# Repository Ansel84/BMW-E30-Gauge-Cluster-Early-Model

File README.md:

# BMW E30 Gauge Cluster Early Model
The goal for this project is to reverse engineer every PCB in the gauge cluster for early model year BMW E30's. This includes the main PCB referred to as the "Nexus" board and the smaller boards that are part of the tachometer and speedometer gauge assemblies. The SI (Service Interval) board has already been successfully reverse engineered and improved by Fabian Gmeiner. His project is linked below. 

## Fabian Gmeiner's SI board project:
https://github.com/FabianGmeiner/BMW_E30_SI_Board

# Progress
08/17/25
The Nexus board is the only board that has been started so far, the other project files are placeholders for now. The Nexus board is nearly complete but still needs to be touched up slightly before being sent off to a manufacturer. Things like via placements, and bulb footprints need to be adjusted as well as verifying the board cut hole locations via a laser cut version. -Ansel84

08/20/25
Begun laser cutting Nexus board tests to ensure that the layout will work before sending off gerbers to be made. Will work on other boards in the meantime. -Ansel84

08/25/25
Started on the speedometer board. Decoded the schematic and layout for the simple speedometer circuit (no O2 sensor indicator circuit). -Ansel84

08/26 - 29/25
Had to find other examples as the one I have only is part of the full circuit. Was able to figure out the circuit from pictures provided by a discord member. -Ansel84

08/30/25
Hall effect sensor PCB replicated. NOTE: if this is ever produced it is only compatible with the Speedometer PCB designed in this project, not compatible with the original board. -Ansel84

09/01/25
speedometer PCB schematic completed. -Ansel84

09/03/25
EG schematic completed. -Ansel84

10/20/25
First run of Nexus board PCB's arrived from JLCPCB. Unfortunately the Connector IV and connector V footprints are not compatible with the original connectors. Also, the fuel gauge location is not quite right, as well as a few lights and screw hole locations. Finally, J1 (Blue connector) location was slightly off. A second set of PCB's will be ordered hopefully fixing these issues. -Ansel84

10/30/25
Updated footprint library to include the coding plug switch and connectors to the EG board. Component locations are in place on this board now. NOTE: double check the locations of J1 and J2 to ensure they are exact, they are only approximate now. -Ansel84

11/01/25
Component locations are complete on the tachometer pcb layout. 

# Late Model Clusters:
If you have a late model cluster and need parts for that, check out the progress of the late model project here: https://github.com/Ansel84/BMW-E30-Gauge-Cluster-Late-Model

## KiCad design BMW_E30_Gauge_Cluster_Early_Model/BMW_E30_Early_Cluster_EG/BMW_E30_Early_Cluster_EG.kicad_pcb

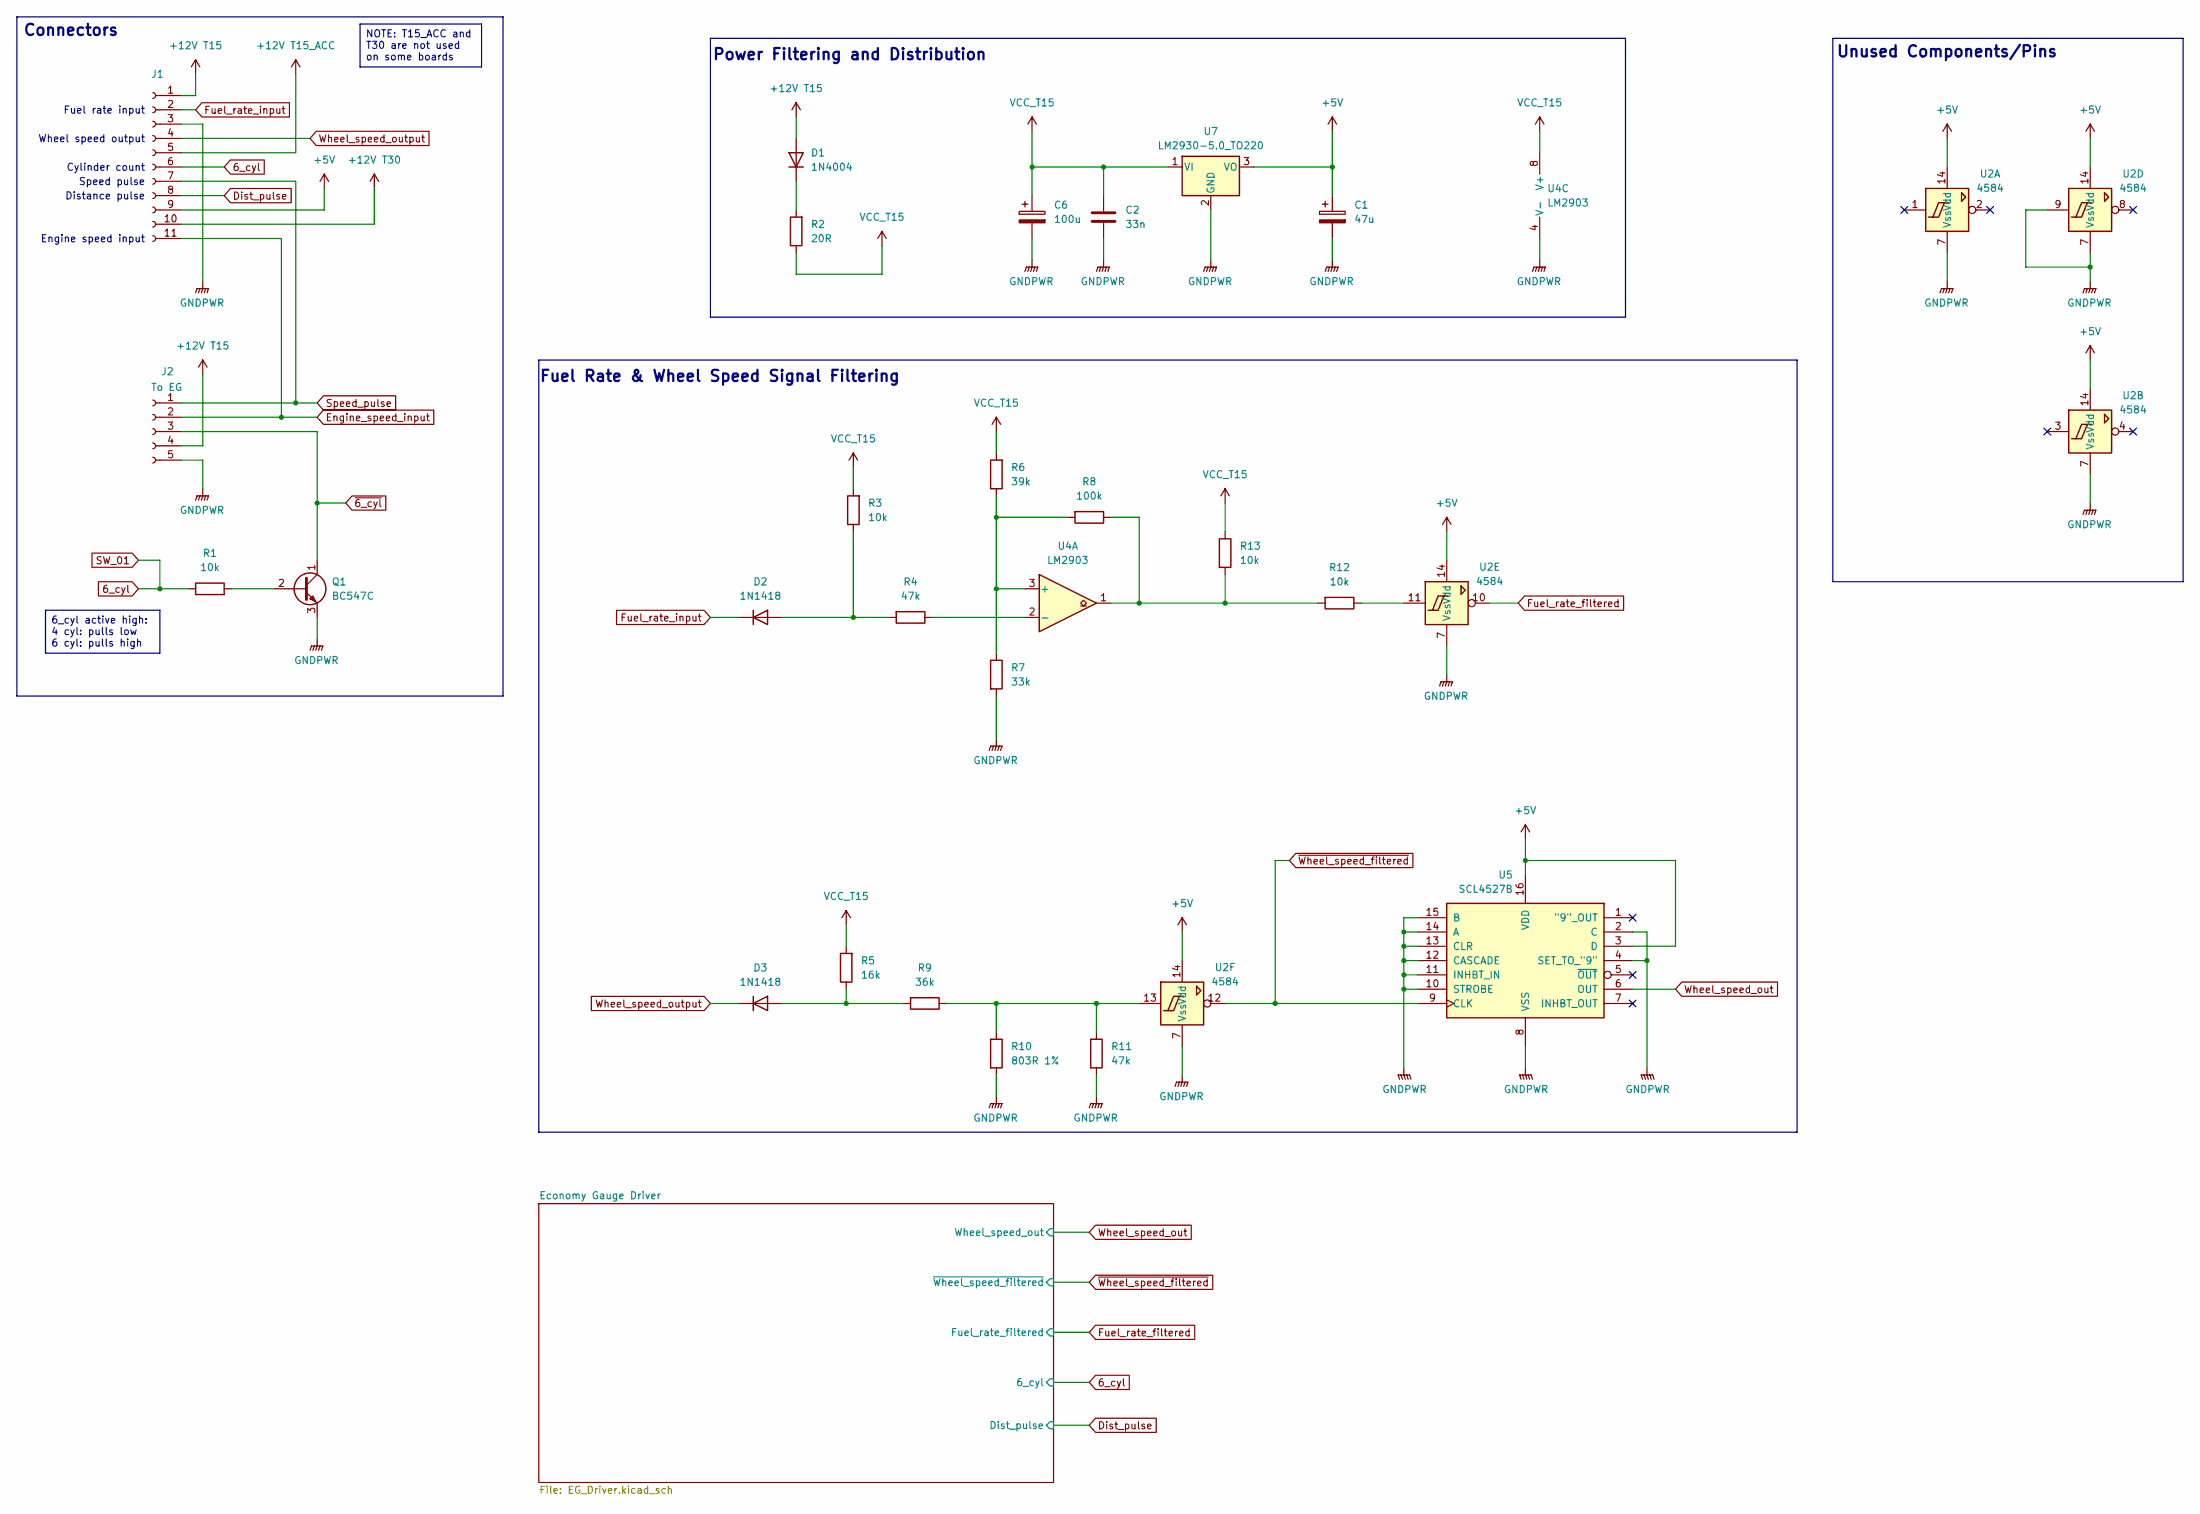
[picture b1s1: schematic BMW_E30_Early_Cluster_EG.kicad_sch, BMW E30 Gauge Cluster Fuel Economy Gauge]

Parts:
C1: 47u; CP_Radial_Tantal_D5.0mm_P2.50mm; Voltage 6.3
C2: 33n; C_Rect_L13.0mm_W4.0mm_P10.00mm_FKS3_FKP3_MKS4; Voltage 250
C6: 100u; CP_Radial_D8.0mm_P5.00mm; Voltage 16
D1: 1N4004; D_DO-41_SOD81_P10.16mm_Horizontal
D2, D3: 1N1418; D_DO-34_SOD68_P10.16mm_Horizontal
J1: Conn_01x11_Socket; ConnectorIV_EG_Socket
J2: To EG; EG_Tach_Socket
Q1: BC547C; TO-92L_Wide
R1, R3, R12, R13: 10k; R_Axial_DIN0207_L6.3mm_D2.5mm_P10.16mm_Horizontal
R2: 20R; R_Axial_DIN0309_L9.0mm_D3.2mm_P20.32mm_Horizontal
R4, R11: 47k; R_Axial_DIN0207_L6.3mm_D2.5mm_P10.16mm_Horizontal
R5: 16k; R_Axial_DIN0207_L6.3mm_D2.5mm_P10.16mm_Horizontal
R6: 39k; R_Axial_DIN0207_L6.3mm_D2.5mm_P10.16mm_Horizontal
R7: 33k; R_Axial_DIN0207_L6.3mm_D2.5mm_P10.16mm_Horizontal
R8: 100k; R_Axial_DIN0207_L6.3mm_D2.5mm_P10.16mm_Horizontal
R9: 36k; R_Axial_DIN0207_L6.3mm_D2.5mm_P10.16mm_Horizontal
R10: 803R 1%; R_Axial_DIN0207_L6.3mm_D2.5mm_P10.16mm_Horizontal
U2: 4584; DIP-14_W7.62mm_Socket_LongPads
U4: LM2903; DIP-8_W7.62mm_Socket
U5: SCL4527B; DIP-16_W7.62mm_Socket_LongPads
U7: LM2930-5.0_TO220; TO-220-3_Vertical

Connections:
6_cyl: J1.6, R1.1; also elsewhere on the board
+5V: C1.1, J1.9, U2.14 (Vdd), U5.3 (D), U5.16 (VDD), U7.3 (VO); also elsewhere on the board
+12V T15: D1.2 (A), J1.1, J2.4
+12V T15_ACC: J1.5
+12V T30: J1.10
Dist_pulse: J1.8; also elsewhere on the board
Engine_speed_input: J1.11, J2.2
Fuel_rate_filtered: U2.10; also elsewhere on the board
Fuel_rate_input: D2.1 (K), J1.2
GNDPWR: C1.2, C2.2, C6.2, J1.3, J2.5, Q1.3 (E), R7.2, R10.2, R11.2, U2.7 (Vss), U2.9, U4.4 (V-), U5.2 (C), U5.4 (SET_TO_"9"), U5.8 (VSS), U5.10 (STROBE), U5.11 (INHBT_IN), U5.12 (CASCADE), U5.13 (CLR), U5.14 (A), U5.15 (B), U7.2 (GND); also elsewhere on the board
unnamed: D1.1 (K), R2.2
unnamed: D2.2 (A), R3.1, R4.2
unnamed: D3.2 (A), R5.1, R9.2
unnamed: Q1.2 (B), R1.2
unnamed: R9.1, R10.1, R11.1, U2.13
unnamed: R12.1, U2.11
unnamed: R8.1, R12.2, R13.2, U4.1
unnamed: R6.1, R7.1, R8.2, U4.3 (+)
unnamed: R4.1, U4.2 (-)
Speed_pulse: J1.7, J2.1
VCC_T15: C2.1, C6.1, R2.1, R3.2, R5.2, R6.2, R13.1, U4.8 (V+), U7.1 (VI); also elsewhere on the board
Wheel_speed_out: U5.6 (OUT); also elsewhere on the board
Wheel_speed_output: D3.1 (K), J1.4
~6_cyl: J2.3, Q1.1 (C)
~Wheel_speed_filtered: U2.12, U5.9 (CLK); also elsewhere on the board

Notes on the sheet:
Speed pulse
Power Filtering and Distribution
Distance pulse
Fuel rate input
Wheel speed output
Fuel Rate & Wheel Speed Signal Filtering
Unused Components/Pins
Connectors
Engine speed input
Cylinder count
6_cyl active high: 4 cyl: pulls low 6 cyl: pulls high
NOTE: T15_ACC and T30 are not used on some boards

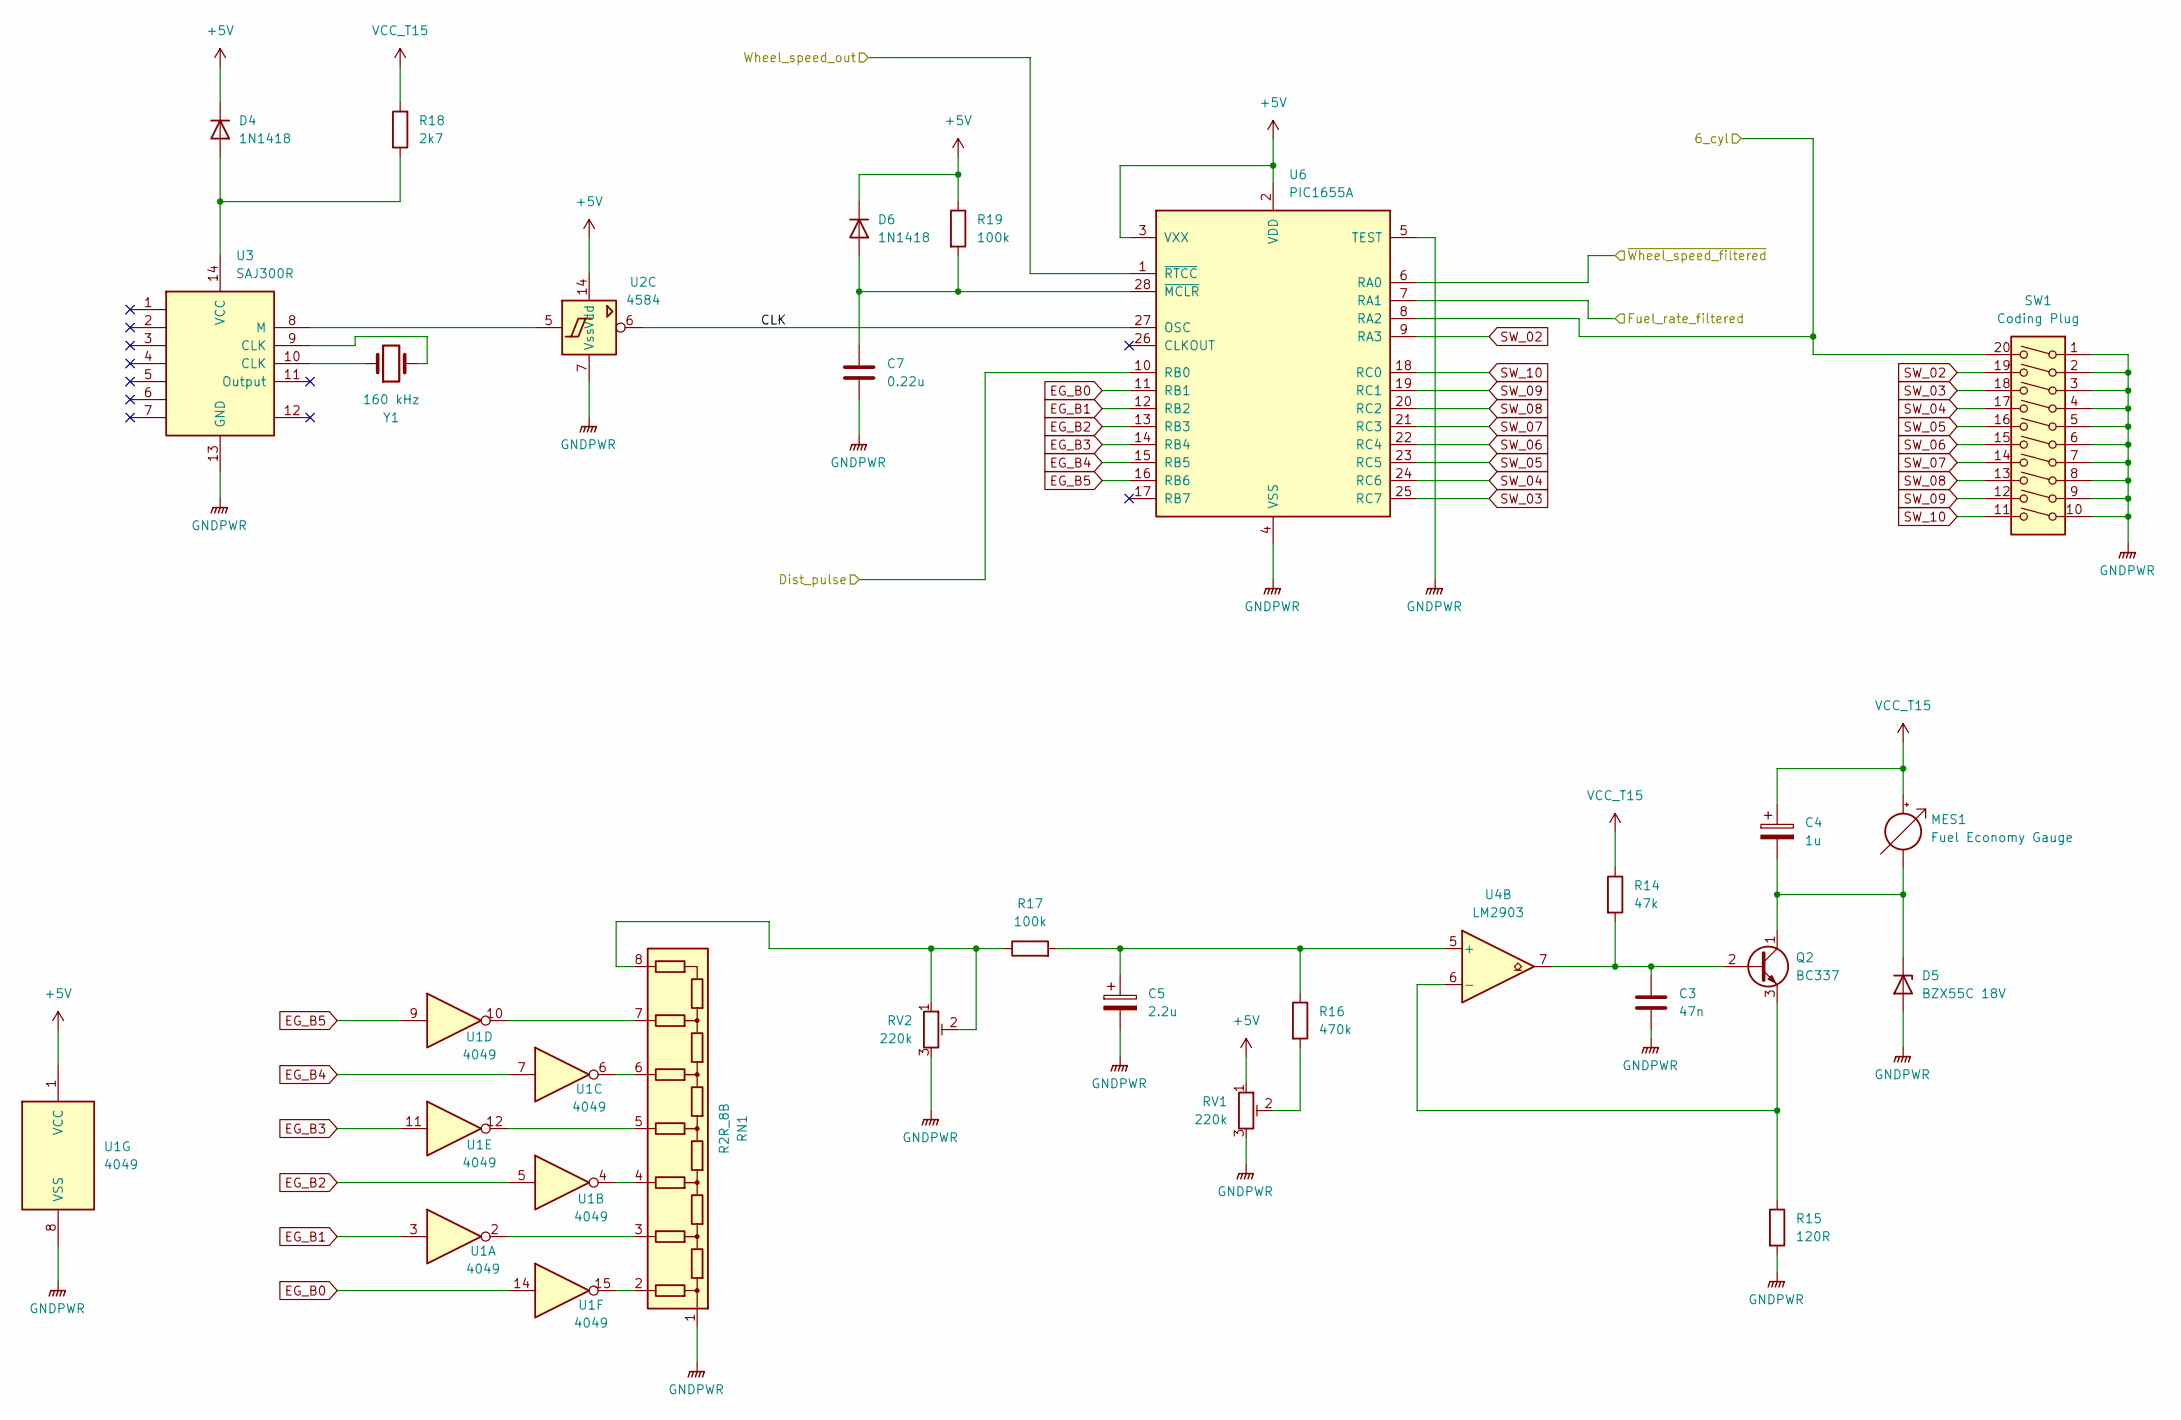
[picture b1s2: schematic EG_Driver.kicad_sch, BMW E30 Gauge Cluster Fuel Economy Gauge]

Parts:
C3: 47n; C_Rect_L13.0mm_W4.0mm_P10.00mm_FKS3_FKP3_MKS4; Voltage 250
C4: 1u; CP_Radial_Tantal_D5.0mm_P2.50mm; Voltage 35
C5: 2.2u; CP_Radial_Tantal_D4.5mm_P2.50mm; Voltage 25
C7: 0.22u; C_Rect_L10.0mm_W3.0mm_P7.50mm_FKS3_FKP3; Voltage 63
D4, D6: 1N1418; D_DO-34_SOD68_P10.16mm_Horizontal
D5: BZX55C 18V; D_DO-34_SOD68_P10.16mm_Horizontal
MES1: Fuel Economy Gauge; Connector_EG
Q2: BC337; TO-92L_Wide
R14: 47k; R_Axial_DIN0207_L6.3mm_D2.5mm_P10.16mm_Horizontal
R15: 120R; R_Axial_DIN0207_L6.3mm_D2.5mm_P10.16mm_Horizontal
R16: 470k; R_Axial_DIN0207_L6.3mm_D2.5mm_P10.16mm_Horizontal
R17, R19: 100k; R_Axial_DIN0207_L6.3mm_D2.5mm_P10.16mm_Horizontal
R18: 2k7; R_Axial_DIN0207_L6.3mm_D2.5mm_P10.16mm_Horizontal
RN1: R2R_8B; R_Array_SIP8
RV1, RV2: 220k; Potentiometer_ACP_CA9-H2,5_Horizontal
SW1: Coding Plug; Coding_Plug
U1: 4049; DIP-16_W7.62mm_Socket
U2: 4584
U3: SAJ300R; DIP-14_W7.62mm_Socket_LongPads
U4: LM2903; DIP-8_W7.62mm_Socket
U6: PIC1655A; DIP-28_W15.24mm
Y1: 160 kHz; Crystal_HC49-U_Vertical

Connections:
6_cyl: SW1.20, U6.8 (RA2); also elsewhere on the board
+5V: D4.1 (K), D6.1 (K), R19.1, RV1.1, U1.1 (VCC), U2.14 (Vdd), U6.2 (VDD), U6.3 (VXX); also elsewhere on the board
/Economy Gauge Driver/CLK: U2.6, U6.27 (OSC)
Dist_pulse: U6.10 (RB0); also elsewhere on the board
EG_B0: U1.14, U6.11 (RB1)
EG_B1: U1.3, U6.12 (RB2)
EG_B2: U1.5, U6.13 (RB3)
EG_B3: U1.11, U6.14 (RB4)
EG_B4: U1.7, U6.15 (RB5)
EG_B5: U1.9, U6.16 (RB6)
Fuel_rate_filtered: U6.7 (RA1); also elsewhere on the board
GNDPWR: C3.2, C5.2, C7.2, D5.2 (A), R15.2, RN1.1 (Bit_out), RV1.3, RV2.3, SW1.1, SW1.2, SW1.3, SW1.4, SW1.5, SW1.6, SW1.7, SW1.8, SW1.9, SW1.10, U1.8 (VSS), U2.7 (Vss), U3.13 (GND), U6.4 (VSS), U6.5 (TEST); also elsewhere on the board
unnamed: D4.2 (A), R18.1, U3.14 (VCC)
unnamed: C4.2, D5.1 (K), MES1.1 (-), Q2.1 (C)
unnamed: C7.1, D6.2 (A), R19.2, U6.28 (~MCLR)
unnamed: C3.1, Q2.2 (B), R14.2, U4.7
unnamed: Q2.3 (E), R15.1, U4.6 (-)
unnamed: R16.2, RV1.2
unnamed: RN1.2 (R1), U1.15
unnamed: RN1.3 (R2), U1.2
unnamed: RN1.4 (R3), U1.4
unnamed: RN1.5 (R4), U1.12
unnamed: RN1.6 (R5), U1.6
unnamed: RN1.7 (R6), U1.10
unnamed: R17.1, RN1.8 (R7), RV2.1, RV2.2
unnamed: U3.9 (CLK), Y1.2
unnamed: U3.10 (CLK), Y1.1
unnamed: U2.5, U3.8 (M)
unnamed: C5.1, R16.1, R17.2, U4.5 (+)
SW_02: SW1.19, U6.9 (RA3)
SW_03: SW1.18, U6.25 (RC7)
SW_04: SW1.17, U6.24 (RC6)
SW_05: SW1.16, U6.23 (RC5)
SW_06: SW1.15, U6.22 (RC4)
SW_07: SW1.14, U6.21 (RC3)
SW_08: SW1.13, U6.20 (RC2)
SW_09: SW1.12, U6.19 (RC1)
SW_10: SW1.11, U6.18 (RC0)
VCC_T15: C4.1, MES1.2 (+), R14.1, R18.2; also elsewhere on the board
Wheel_speed_out: U6.1 (~RTCC); also elsewhere on the board
~Wheel_speed_filtered: U6.6 (RA0); also elsewhere on the board

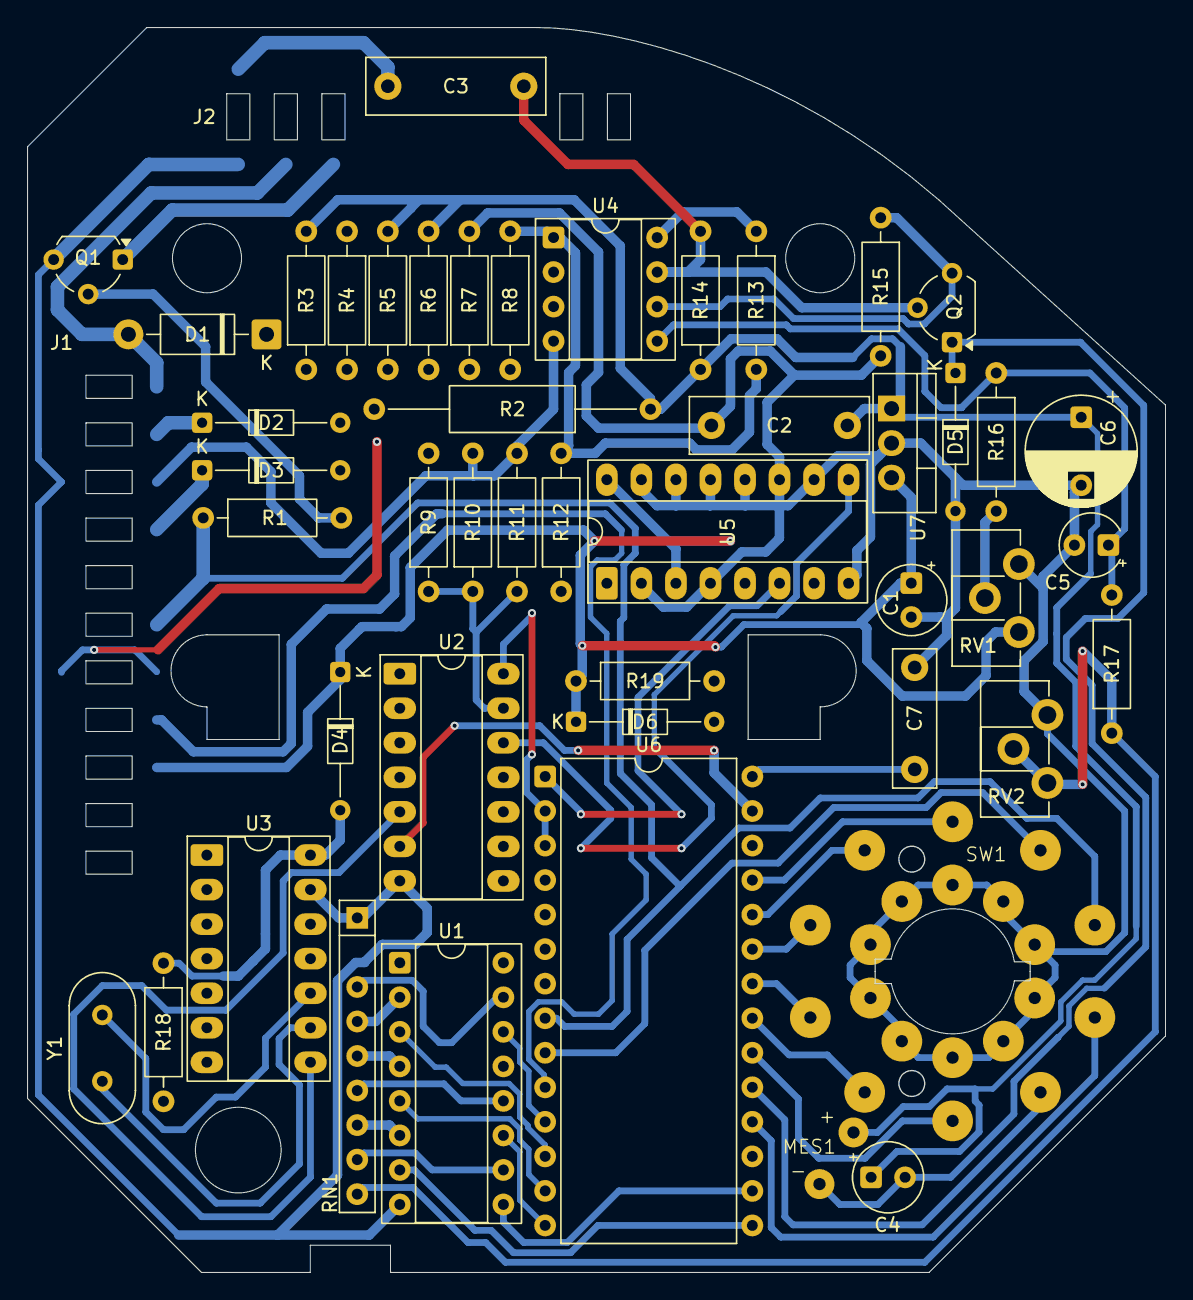
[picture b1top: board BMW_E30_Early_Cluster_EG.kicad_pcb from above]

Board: 2 copper layers, 83.7 x 91.6 mm, 49 parts (0 on the bottom side), 56 nets.

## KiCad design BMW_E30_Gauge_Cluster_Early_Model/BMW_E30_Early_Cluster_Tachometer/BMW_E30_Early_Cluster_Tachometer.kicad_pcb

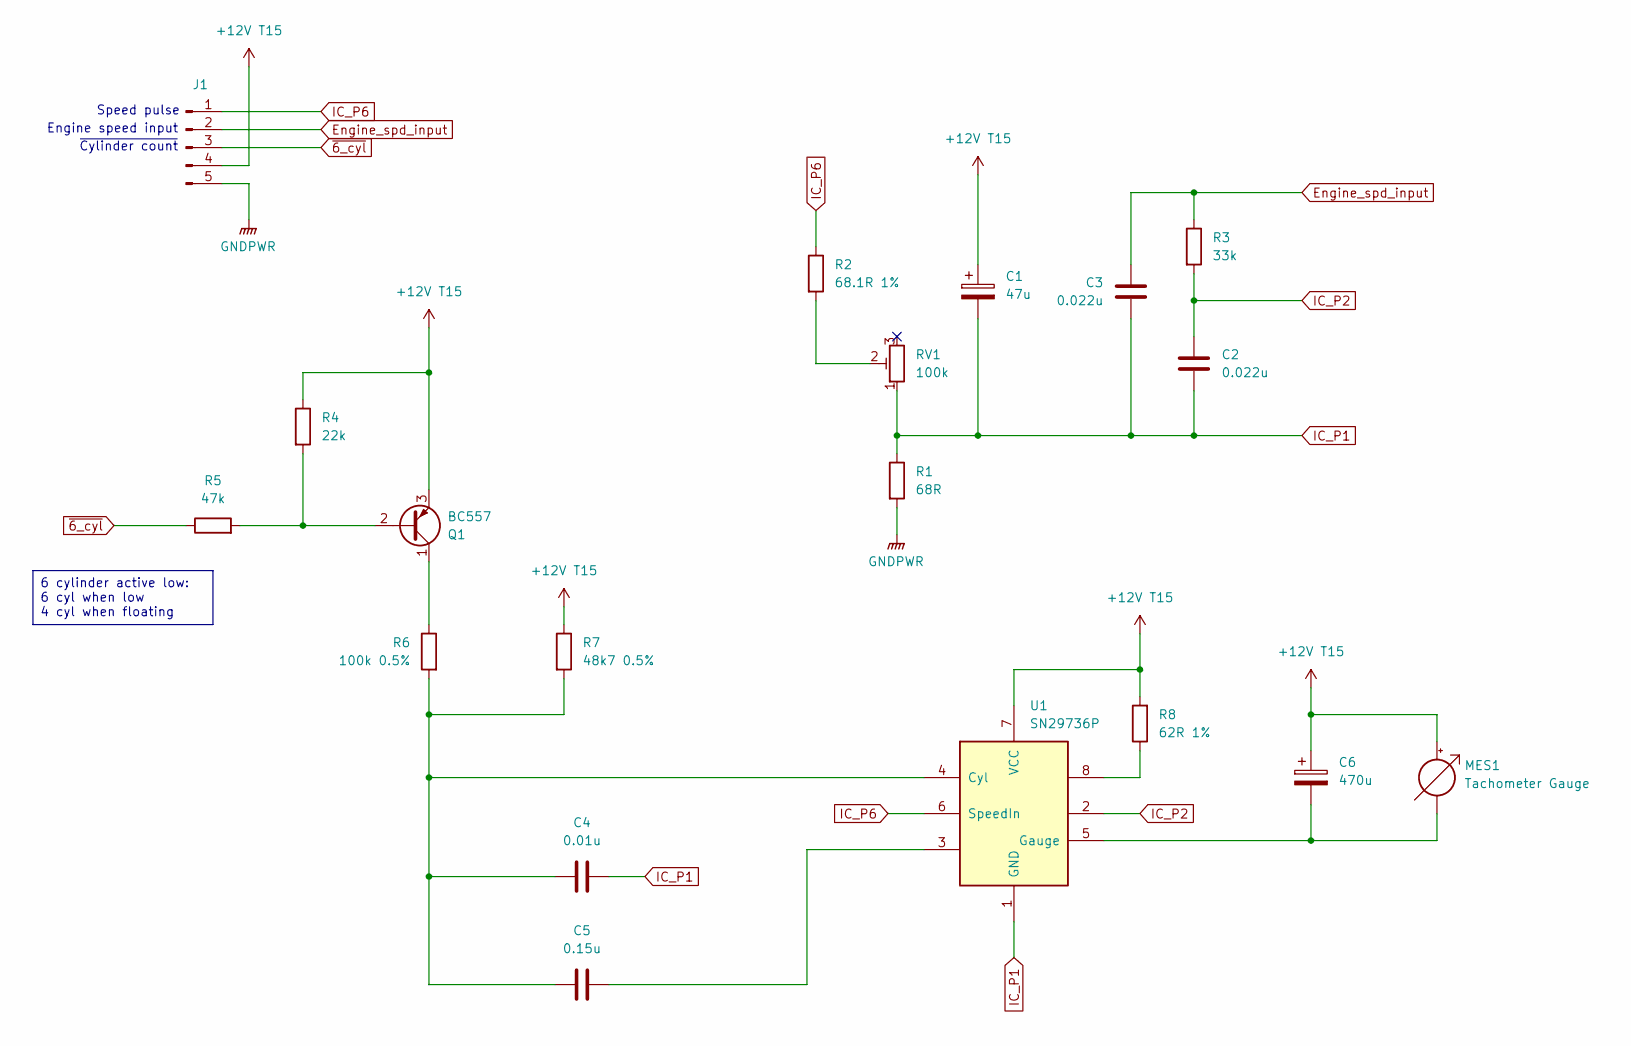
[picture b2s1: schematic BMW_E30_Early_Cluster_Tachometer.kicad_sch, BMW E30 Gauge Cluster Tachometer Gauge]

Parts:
C1: 47u; CP_Axial_L11.0mm_D6.0mm_P18.00mm_Horizontal
C2, C3: 0.022u; C_Axial_L12.0mm_D6.5mm_P15.00mm_Horizontal
C4: 0.01u; C_Disc_D5.0mm_W2.5mm_P5.00mm
C5: 0.15u; C_Axial_L12.0mm_D6.5mm_P15.00mm_Horizontal
C6: 470u; CP_Axial_L25.0mm_D10.0mm_P30.00mm_Horizontal
J1: Conn_01x05_Pin; EG_Tach_Pins
MES1: Tachometer Gauge; Connector_Tach
Q1: BC557; TO-92_Wide
R1: 68R; R_Axial_DIN0411_L9.9mm_D3.6mm_P15.24mm_Horizontal
R2: 68.1R 1%; R_Axial_DIN0207_L6.3mm_D2.5mm_P7.62mm_Horizontal
R3: 33k; R_Axial_DIN0207_L6.3mm_D2.5mm_P7.62mm_Horizontal
R4: 22k; R_Axial_DIN0207_L6.3mm_D2.5mm_P7.62mm_Horizontal
R5: 47k; R_Axial_DIN0207_L6.3mm_D2.5mm_P7.62mm_Horizontal
R6: 100k 0.5%; R_Axial_DIN0207_L6.3mm_D2.5mm_P7.62mm_Horizontal
R7: 48k7 0.5%; R_Axial_DIN0207_L6.3mm_D2.5mm_P7.62mm_Horizontal
R8: 62R 1%; R_Axial_DIN0309_L9.0mm_D3.2mm_P15.24mm_Horizontal
RV1: 100k; Potentiometer_Piher_PT-10-V10_Vertical
U1: SN29736P; DIP-8_W7.62mm_Socket_LongPads

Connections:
+12V T15: C1.1, C6.1, J1.4, MES1.2 (+), Q1.3 (E), R4.1, R7.1, R8.2, U1.7 (VCC)
Engine_spd_input: C3.1, J1.2, R3.1
GNDPWR: J1.5, R1.2
IC_P1: C1.2, C2.2, C3.2, C4.1, R1.1, RV1.1, U1.1 (GND)
IC_P2: C2.1, R3.2, U1.2
IC_P6: J1.1, R2.1, U1.6 (SpeedIn)
unnamed: C5.1, U1.3
unnamed: C6.2, MES1.1 (-), U1.5 (Gauge)
unnamed: Q1.2 (B), R4.2, R5.2
unnamed: Q1.1 (C), R6.1
unnamed: R2.2, RV1.2
unnamed: R8.1, U1.8
unnamed: C4.2, C5.2, R6.2, R7.2, U1.4 (Cyl)
~6_cyl: J1.3, R5.1

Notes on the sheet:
Speed pulse
Engine speed input
~{Cylinder count}
6 cylinder active low: 6 cyl when low 4 cyl when floating

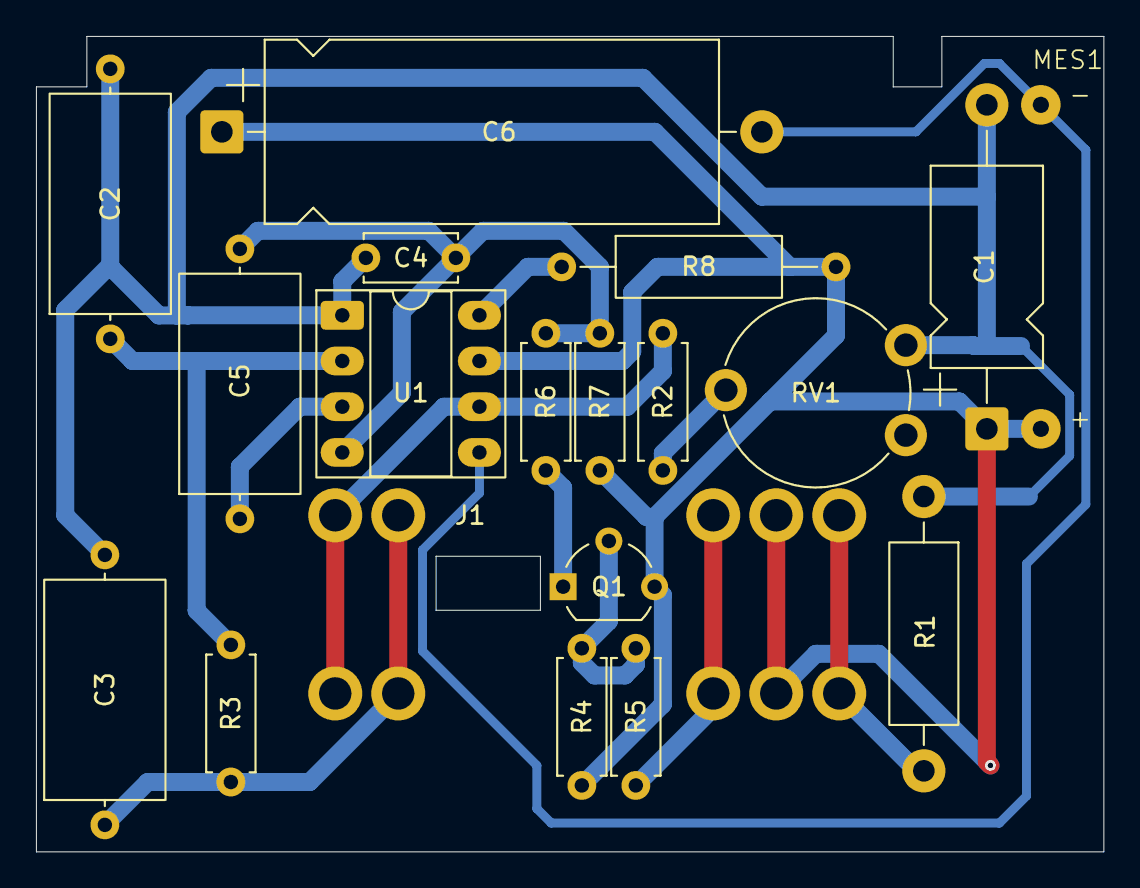
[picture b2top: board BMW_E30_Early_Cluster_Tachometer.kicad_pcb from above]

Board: 2 copper layers, 59.3 x 45.3 mm, 19 parts (0 on the bottom side), 14 nets.

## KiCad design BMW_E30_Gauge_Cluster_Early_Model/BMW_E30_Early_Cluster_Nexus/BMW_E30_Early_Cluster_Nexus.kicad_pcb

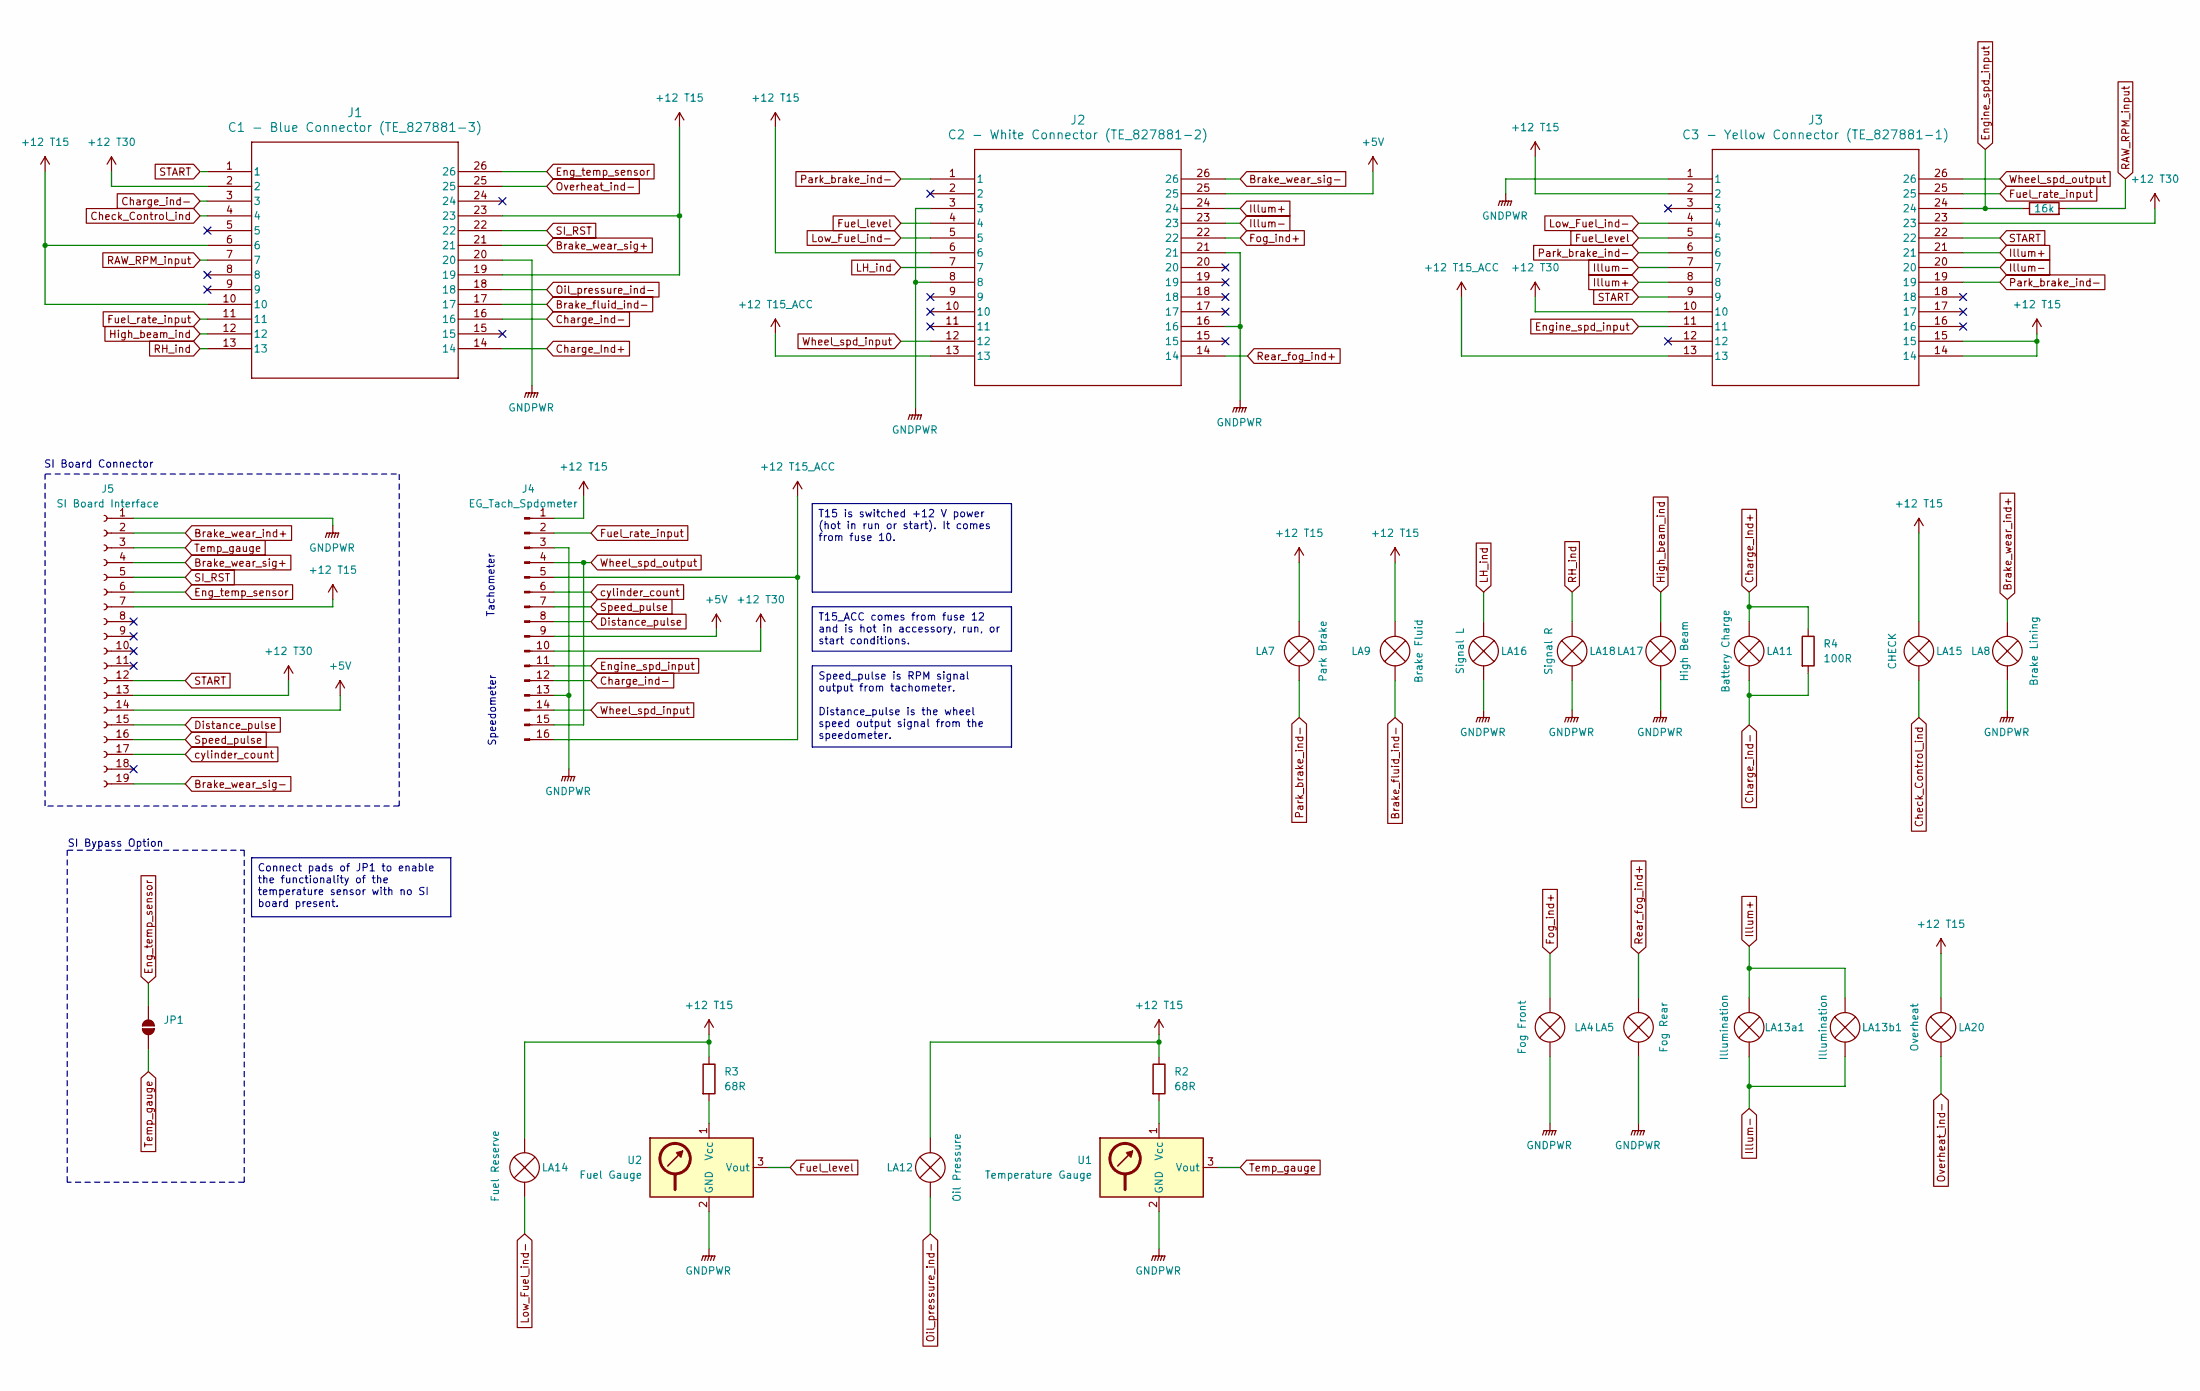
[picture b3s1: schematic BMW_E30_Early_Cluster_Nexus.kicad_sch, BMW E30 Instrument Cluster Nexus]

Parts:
J1: C1 - Blue Connector (TE_827881-3); TE_827881-3; Digikey Part No. 827881-3-ND
J2: C2 - White Connector (TE_827881-2); TE_827881-2; Digikey Part No. A129100-ND
J3: C3 - Yellow Connector (TE_827881-1); TE_827881-1; Digikey Part No. A129099-ND
J4: EG_Tach_Spdometer; ConnectorIV_Early
J5: SI Board Interface; ConnectorV_Early_V2
JP1: SI BYPASS; SolderJumper-2_P1.3mm_Open_RoundedPad1.0x1.5mm
LA4: Fog Front; 2721MF
LA5: Fog Rear; 2721MF
LA7: Park Brake; 2721MF
LA8: Brake Lining; 2721MF
LA9: Brake Fluid; 2721MF
LA11: Battery Charge; 2821MF
LA12: Oil Pressure; 2721MF
LA13a1, LA13b1: Illumination; 2821MF
LA14: Fuel Reserve; 2721MF
LA15: CHECK; 2721MF
LA16: Signal L; 2721MF
LA17: High Beam; 2721MF
LA18: Signal R; 2721MF
LA20: Overheat; 2721MF
R1: 16k; R_Axial_DIN0207_L6.3mm_D2.5mm_P10.16mm_Horizontal; Digikey Part No. CF14JT16K0CT-ND
R2, R3: 68R; R_Axial_DIN0516_L15.5mm_D5.0mm_P20.32mm_Horizontal; Digikey Part No. 2019-PCF1C680K-ND
R4: 100R; R_Axial_DIN0414_L11.9mm_D4.5mm_P15.24mm_Horizontal; Digikey Part No. 541-CMF65100R00FKEBCT-ND
U1: Temperature Gauge; Gauge_Temp
U2: Fuel Gauge; Gauge_Fuel

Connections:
+5V: J2.25, J4.9, J5.14
+12 T15: J1.6, J1.10, J1.19, J1.23, J2.6, J3.2, J3.14, J3.15, J4.1, J5.7, LA7.2 (+), LA9.2 (+), LA12.2 (+), LA14.1 (-), LA15.1 (-), LA20.1 (-), R2.1, R3.1
+12 T15_ACC: J2.13, J3.13, J4.5, J4.16
+12 T30: J1.2, J3.10, J3.23, J4.10, J5.13
Brake_fluid_ind-: J1.17, LA9.1 (-)
Brake_wear_ind+: J5.2, LA8.2 (+)
Brake_wear_sig+: J1.21, J5.4
Brake_wear_sig-: J2.26, J5.19
Charge_Ind+: J1.14, LA11.1 (-), R4.1
Charge_ind-: J1.3, J1.16, J4.12, LA11.2 (+), R4.2
Check_Control_ind: J1.4, LA15.2 (+)
Distance_pulse: J4.8, J5.15
Eng_temp_sensor: J1.26, J5.6, JP1.2 (B)
Engine_spd_input: J3.11, J3.24, J4.11, R1.1
Fog_ind+: J2.22, LA4.1 (-)
Fuel_level: J2.4, J3.5, U2.3 (Vout)
Fuel_rate_input: J1.11, J3.25, J4.2
GNDPWR: J1.20, J2.3, J2.8, J2.16, J2.21, J3.1, J4.3, J4.13, J5.1, LA4.2 (+), LA5.1 (-), LA8.1 (-), LA16.2 (+), LA17.1 (-), LA18.2 (+), U1.2 (GND), U2.2 (GND)
High_beam_ind: J1.12, LA17.2 (+)
Illum+: J2.24, J3.8, J3.21, LA13a1.1 (-), LA13b1.1 (-)
Illum-: J2.23, J3.7, J3.20, LA13a1.2 (+), LA13b1.2 (+)
LH_ind: J2.7, LA16.1 (-)
Low_Fuel_ind-: J2.5, J3.4, LA14.2 (+)
unnamed: R2.2, U1.1 (Vcc)
unnamed: R3.2, U2.1 (Vcc)
Oil_pressure_ind-: J1.18, LA12.1 (-)
Overheat_ind-: J1.25, LA20.2 (+)
Park_brake_ind-: J2.1, J3.6, J3.19, LA7.1 (-)
RAW_RPM_input: J1.7, R1.2
RH_ind: J1.13, LA18.1 (-)
Rear_fog_ind+: J2.14, LA5.2 (+)
SI_RST: J1.22, J5.5
START: J1.1, J3.9, J3.22, J5.12
Speed_pulse: J4.7, J5.16
Temp_gauge: J5.3, JP1.1 (A), U1.3 (Vout)
Wheel_spd_input: J2.12, J4.14
Wheel_spd_output: J3.26, J4.4, J4.15
cylinder_count: J4.6, J5.17

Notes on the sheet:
SI Board Connector
Speedometer
SI Bypass Option
Tachometer
T15_ACC comes from fuse 12 and is hot in accessory, run, or start conditions.
T15 is switched +12 V power (hot in run or start). It comes from fuse 10.
Connect pads of JP1 to enable the functionality of the temperature sensor with no SI board present.
Speed_pulse is RPM signal output from tachometer. Distance_pulse is the wheel speed output signal from the speedometer.

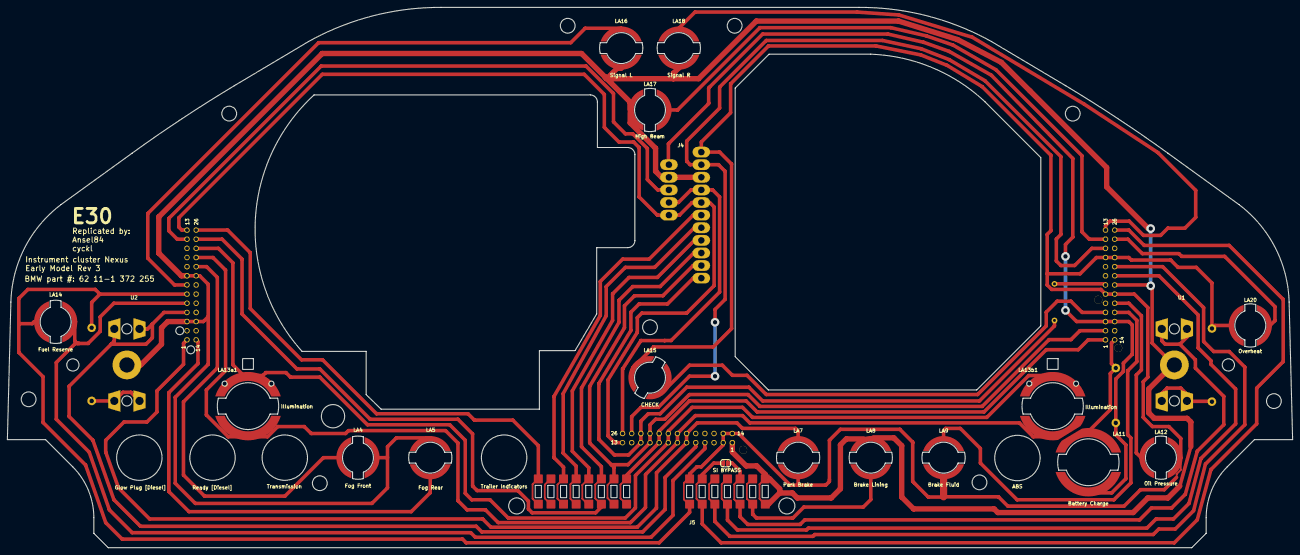
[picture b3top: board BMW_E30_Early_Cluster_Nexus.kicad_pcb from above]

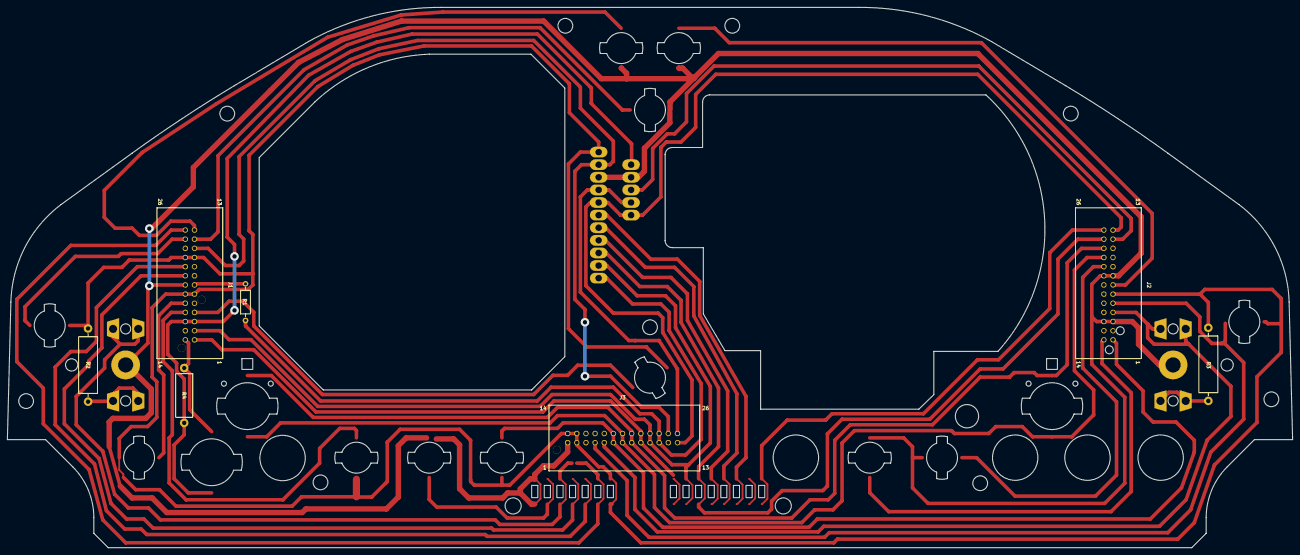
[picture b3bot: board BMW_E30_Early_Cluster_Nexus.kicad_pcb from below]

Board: 2 copper layers, 356.8 x 150.0 mm, 27 parts (7 on the bottom side), 38 nets.
